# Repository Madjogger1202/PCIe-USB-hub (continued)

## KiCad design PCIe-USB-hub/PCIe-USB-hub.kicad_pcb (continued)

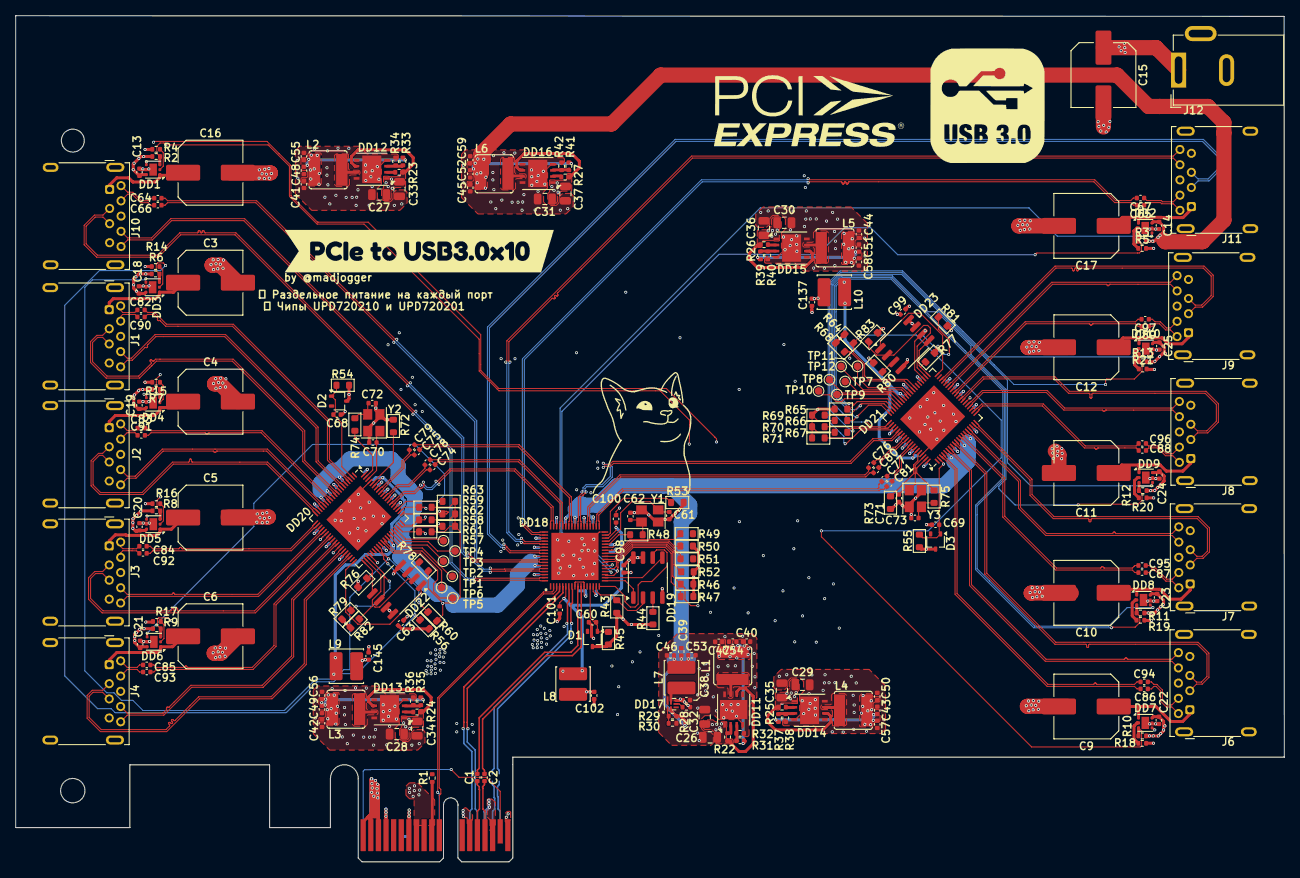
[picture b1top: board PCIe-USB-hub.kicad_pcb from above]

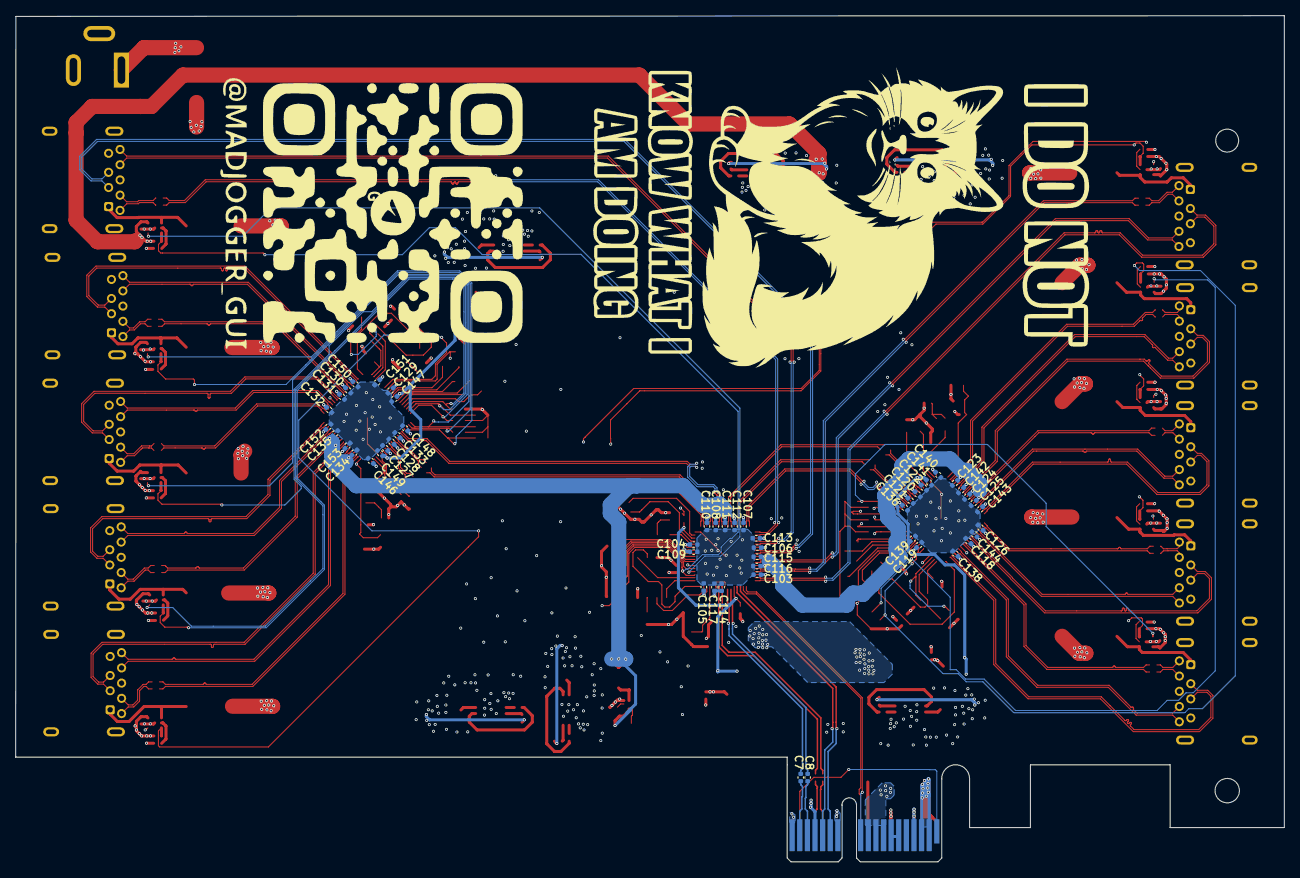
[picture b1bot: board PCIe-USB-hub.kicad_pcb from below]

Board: 4 copper layers, 166.7 x 111.2 mm, 300 parts (51 on the bottom side), 235 nets.

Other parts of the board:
kibuzzard-67F2EEE1: G***; kibuzzard-67F2EEE1

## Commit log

2025-03-13 вводный коммит
2025-03-14 Добавил gitignore
2025-03-14 Создал основные компоненты, поставил на схеме
2025-03-17 Частично добавил компоненты
2025-03-22 Изменение иерархии схемы + на схеме теперь все линии USB соединены
2025-03-23 Исправил отсутствие перекрёстного соединения на PCIe
2025-03-23 Чут изменений
2025-03-26 Доработка схемы, частичная конфигурация чипов
2025-03-27 Чут чут модифицировал
2025-03-28 Доделал схему, сделал контур платы и расстановку предварительную USB портов
2025-03-31 тык тык поменял разъёмы на одинарные
2025-03-31 натыкал трассировку всех дифф линий, поменял часть местами для удобной трассировки
2025-04-06 тык-перетык
